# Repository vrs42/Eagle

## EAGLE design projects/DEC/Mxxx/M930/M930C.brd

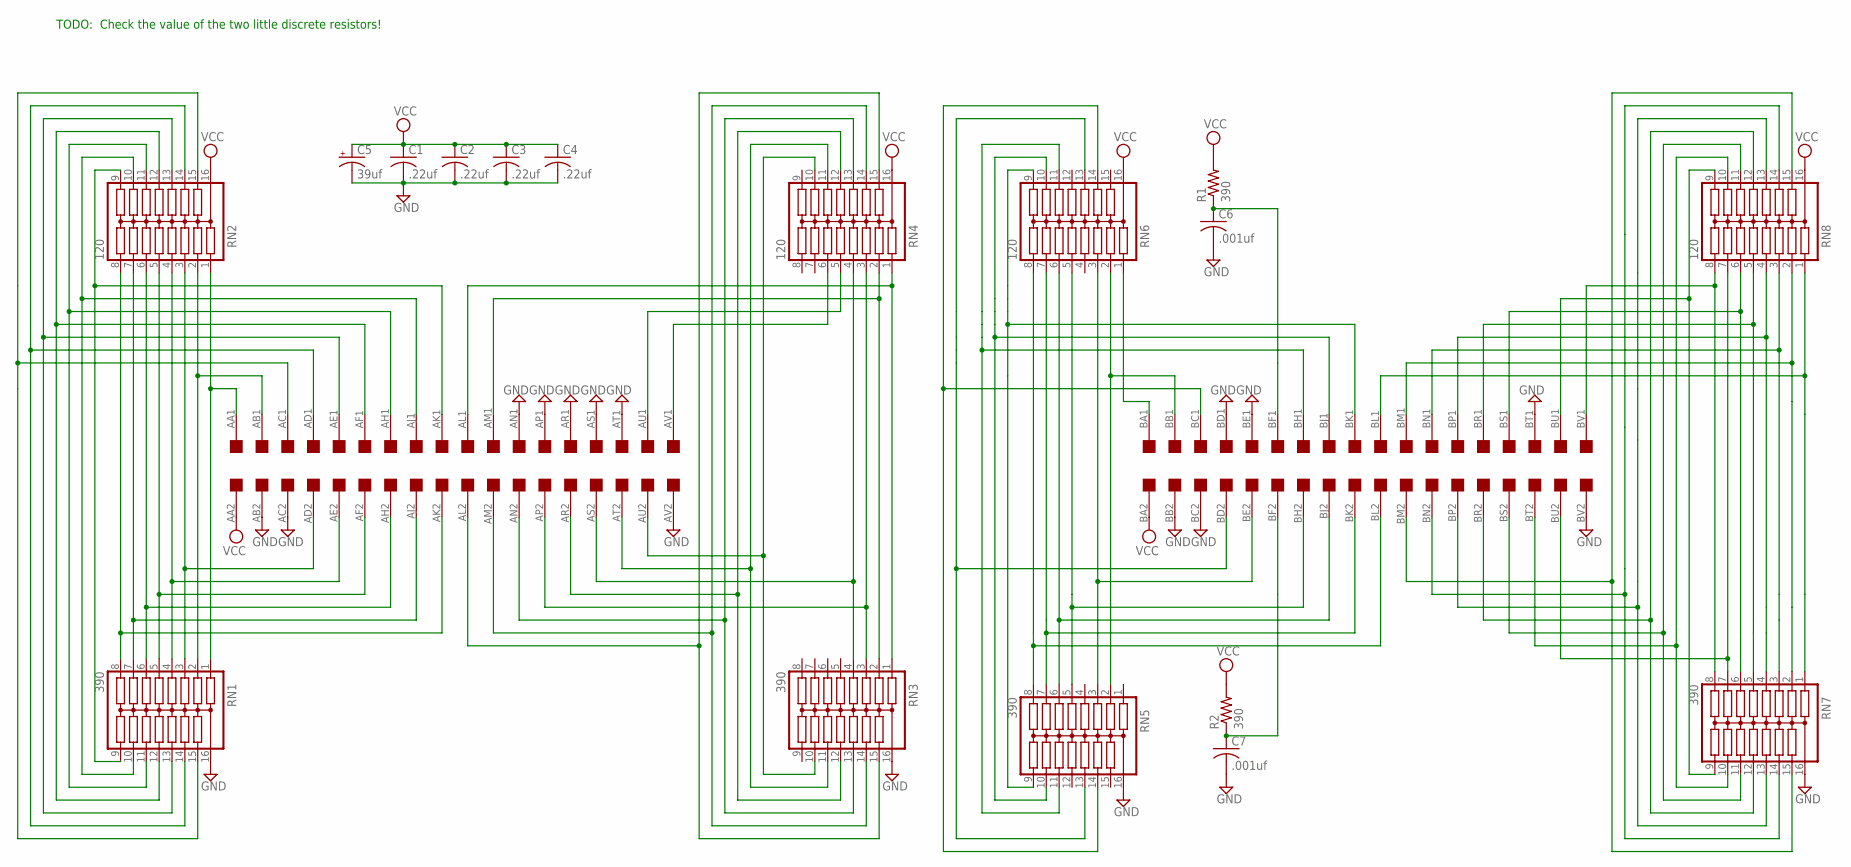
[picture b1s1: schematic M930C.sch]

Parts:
C1, C2, C3, C4: .22uf; C050-025X075
C5: 39uf; E15-5
C6, C7: .001uf; C050-025X075
R1, R2: 390; 0207/10
RN1, RN3, RN5, RN7: 390; DIL16
RN2, RN4, RN6, RN8: 120; DIL16
U$1: DOUBLE; EDGE-CON4

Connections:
AA1: RN1.1, RN2.1, U$1.AA1
AB1: RN1.2, RN2.2, U$1.AB1
AC1: RN1.15, RN2.15, U$1.AC1
AD1: RN1.14, RN2.14, U$1.AD1
AD2: RN1.3, RN2.3, U$1.AD2
AE1: RN1.13, RN2.13, U$1.AE1
AE2: RN1.4, RN2.4, U$1.AE2
AF1: RN1.12, RN2.12, U$1.AF1
AF2: RN1.5, RN2.5, U$1.AF2
AH1: RN1.11, RN2.11, U$1.AH1
AH2: RN1.6, RN2.6, U$1.AH2
AJ1: RN1.10, RN2.10, U$1.AJ1
AJ2: RN1.7, RN2.7, U$1.AJ2
AK1: RN1.9, RN2.9, U$1.AK1
AK2: RN1.8, RN2.8, U$1.AK2
AL1: RN3.1, RN4.1, U$1.AL1
AL2: RN3.15, RN4.15, U$1.AL2
AM1: RN3.2, RN4.2, U$1.AM1
AM2: RN3.14, RN4.14, U$1.AM2
AN2: RN3.13, RN4.13, U$1.AN2
AP2: RN3.3, RN4.3, U$1.AP2
AR2: RN3.12, RN4.12, U$1.AR2
AS2: RN3.4, RN4.4, U$1.AS2
AT2: RN3.11, RN4.11, U$1.AT2
AU1: RN4.5, U$1.AU1
AU2: RN3.10, RN4.10, U$1.AU2
AV1: RN4.6, U$1.AV1
BA1: RN6.1, U$1.BA1
BB1: RN5.2, RN6.2, U$1.BB1
BC1: RN5.14, RN6.14, U$1.BC1
BD2: RN5.13, RN6.13, U$1.BD2
BE2: RN5.3, RN6.3, U$1.BE2
BH1: RN5.11, RN6.11, U$1.BH1
BH2: RN5.5, RN6.5, U$1.BH2
BJ1: RN5.10, RN6.10, U$1.BJ1
BJ2: RN5.6, RN6.6, U$1.BJ2
BK1: RN5.9, RN6.9, U$1.BK1
BK2: RN5.7, RN6.7, U$1.BK2
BL1: RN7.1, RN8.1, U$1.BL1
BL2: RN5.8, RN6.8, U$1.BL2
BM1: RN7.2, RN8.2, U$1.BM1
BM2: RN7.15, RN8.15, U$1.BM2
BN1: RN7.3, RN8.3, U$1.BN1
BN2: RN7.14, RN8.14, U$1.BN2
BP1: RN7.4, RN8.4, U$1.BP1
BP2: RN7.13, RN8.13, U$1.BP2
BR1: RN7.5, RN8.5, U$1.BR1
BR2: RN7.12, RN8.12, U$1.BR2
BS1: RN7.6, RN8.6, U$1.BS1
BS2: RN7.11, RN8.11, U$1.BS2
BT2: RN7.10, RN8.10, U$1.BT2
BU1: RN7.9, RN8.9, U$1.BU1
BU2: RN7.7, RN8.7, U$1.BU2
BV1: RN7.8, RN8.8, U$1.BV1
GND: C1.2, C2.2, C3.2, C4.2, C5.-, C6.2, C7.2, RN1.16, RN3.16, RN5.16, RN7.16, U$1.AB2, U$1.AC2, U$1.AN1, U$1.AP1, U$1.AR1, U$1.AS1, U$1.AT1, U$1.AV2, U$1.BB2, U$1.BC2, U$1.BD1, U$1.BE1, U$1.BT1, U$1.BV2
unnamed: C7.1, R2.1, U$1.BF2
unnamed: C6.1, R1.1, U$1.BF1
VCC: C1.1, C2.1, C3.1, C4.1, C5.+, R1.2, R2.2, RN2.16, RN4.16, RN6.16, RN8.16, U$1.AA2, U$1.BA2

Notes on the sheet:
TODO: Check the value of the two little discrete resistors!

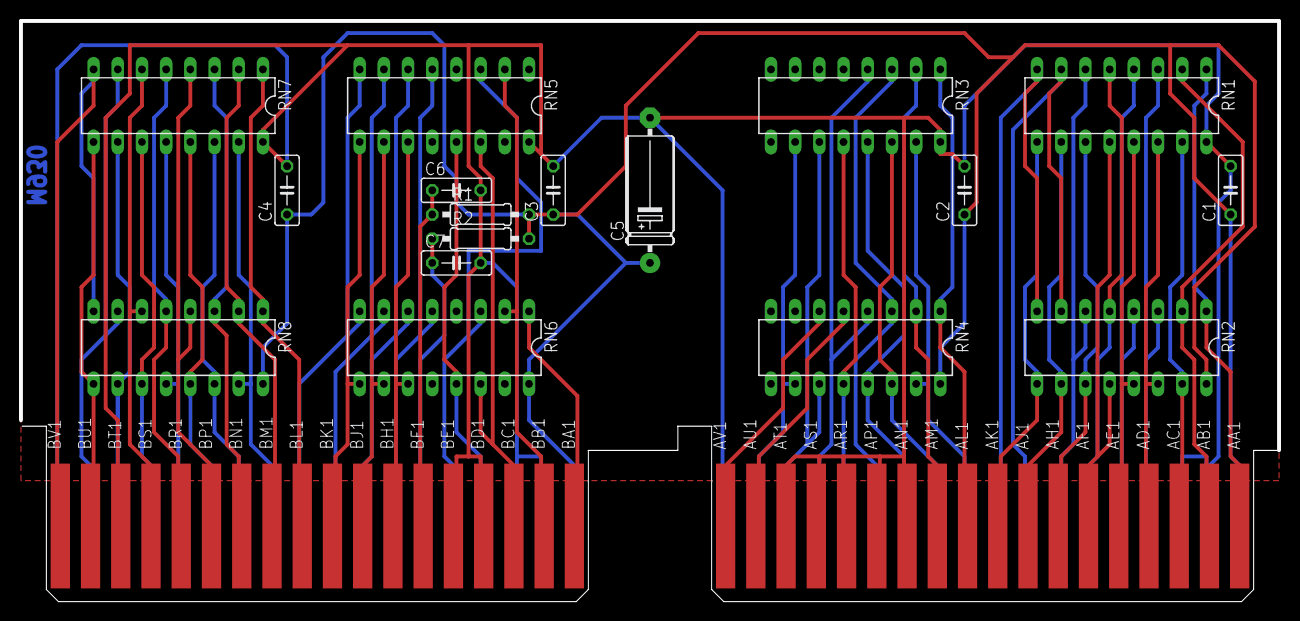
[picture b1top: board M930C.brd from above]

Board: 2 copper layers, 132.1 x 61.0 mm, 18 parts (0 on the bottom side), 58 nets.

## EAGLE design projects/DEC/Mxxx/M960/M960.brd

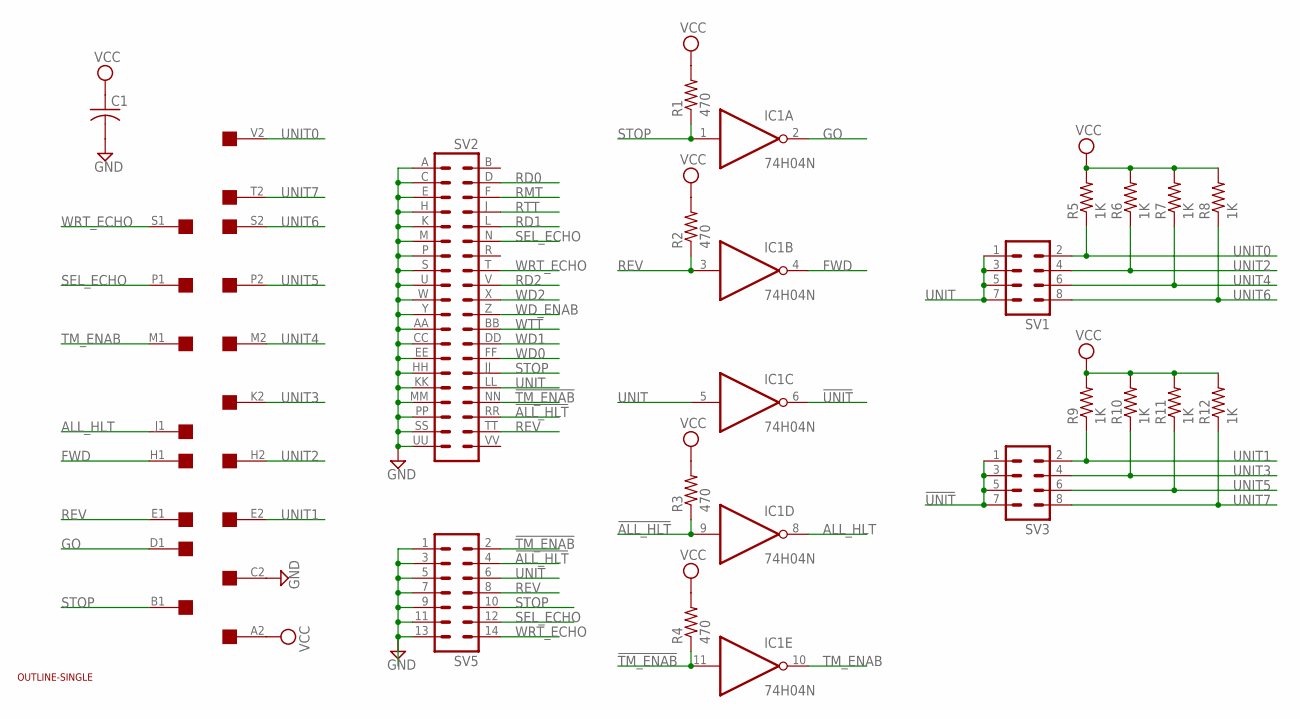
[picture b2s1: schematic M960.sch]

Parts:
C1: C-US050-025X075; C050-025X075
IC1: 74H04N; DIL14
R1, R2, R3, R4: 470; 0207/10
R5, R6, R7, R8, R9, R10, R11, R12: 1K; 0207/10
SV1, SV3: MA04-2
SV2: DEC40PINV
SV5: MA07-2
U$1: OUTLINE-SINGLE; SINGLE
U$2: SINGLE; EDGE-CON2

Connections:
!ALL_HLT: IC1.9 (I), R3.1, SV2.RR (36), SV5.4
!TM_ENAB: IC1.11 (I), R4.1, SV2.NN (34), SV5.2
!UNIT: IC1.6 (O), SV3.1, SV3.3, SV3.5, SV3.7
ALL_HLT: IC1.8 (O), U$2.J1
FWD: IC1.4 (O), U$2.H1
GND: C1.2, IC1.7 (GND), SV2.A (1), SV2.AA (23), SV2.C (3), SV2.CC (25), SV2.E (5), SV2.EE (27), SV2.H (7), SV2.HH (29), SV2.K (9), SV2.KK (31), SV2.M (11), SV2.MM (33), SV2.P (13), SV2.PP (35), SV2.S (15), SV2.SS (37), SV2.U (17), SV2.UU (39), SV2.W (19), SV2.Y (21), SV5.1, SV5.3, SV5.5, SV5.7, SV5.9, SV5.11, SV5.13, U$2.C2
GO: IC1.2 (O), U$2.D1
RD0: SV2.D (4)
RD1: SV2.L (10)
RD2: SV2.V (18)
REV: IC1.3 (I), R2.1, SV2.TT (38), SV5.8, U$2.E1
RMT: SV2.F (6)
RTT: SV2.J (8)
SEL_ECHO: SV2.N (12), SV5.12, U$2.P1
STOP: IC1.1 (I), R1.1, SV2.JJ (30), SV5.10, U$2.B1
TM_ENAB: IC1.10 (O), U$2.M1
UNIT: IC1.5 (I), SV1.1, SV1.3, SV1.5, SV1.7, SV2.LL (32), SV5.6
UNIT0: R5.1, SV1.2, U$2.V2
UNIT1: R9.1, SV3.2, U$2.E2
UNIT2: R6.1, SV1.4, U$2.H2
UNIT3: R10.1, SV3.4, U$2.K2
UNIT4: R7.1, SV1.6, U$2.M2
UNIT5: R11.1, SV3.6, U$2.P2
UNIT6: R8.1, SV1.8, U$2.S2
UNIT7: R12.1, SV3.8, U$2.T2
VCC: C1.1, IC1.14 (VCC), R1.2, R2.2, R3.2, R4.2, R5.2, R6.2, R7.2, R8.2, R9.2, R10.2, R11.2, R12.2, U$2.A2
WD0: SV2.FF (28)
WD1: SV2.DD (26)
WD2: SV2.X (20)
WD_ENAB: SV2.Z (22)
WRT_ECHO: SV2.T (16), SV5.14, U$2.S1
WTT: SV2.BB (24)

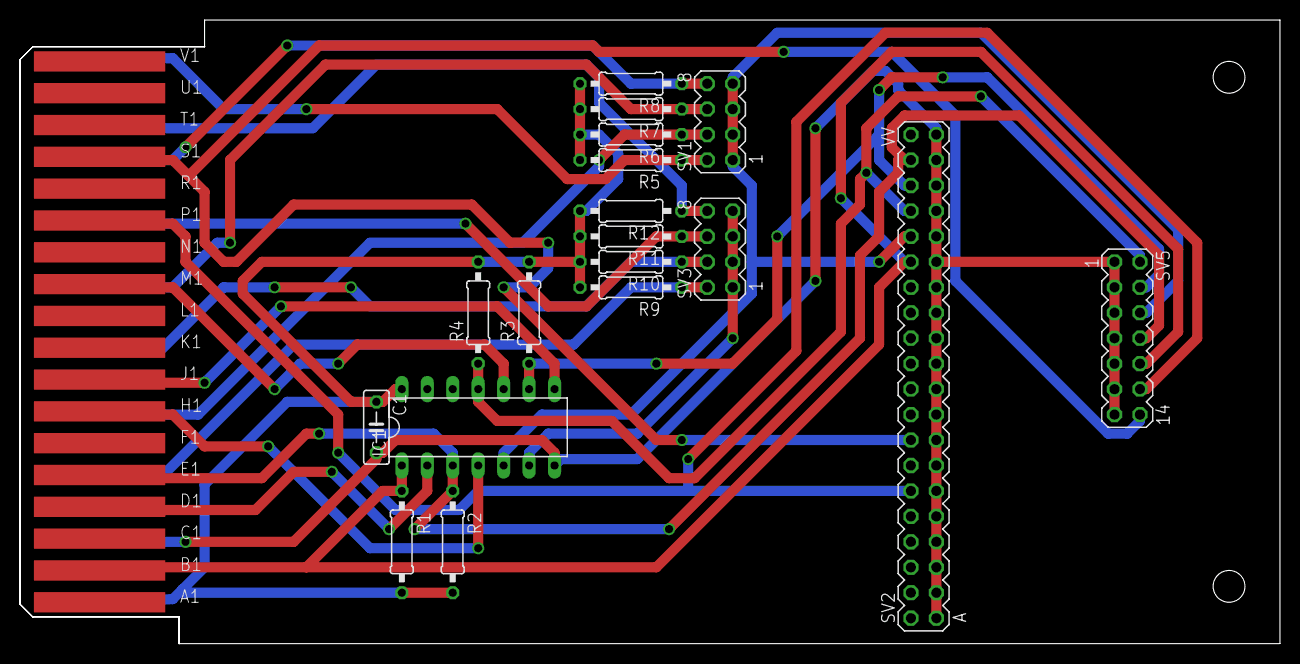
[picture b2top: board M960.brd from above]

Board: 2 copper layers, 125.7 x 62.2 mm, 20 parts (0 on the bottom side), 22 nets.

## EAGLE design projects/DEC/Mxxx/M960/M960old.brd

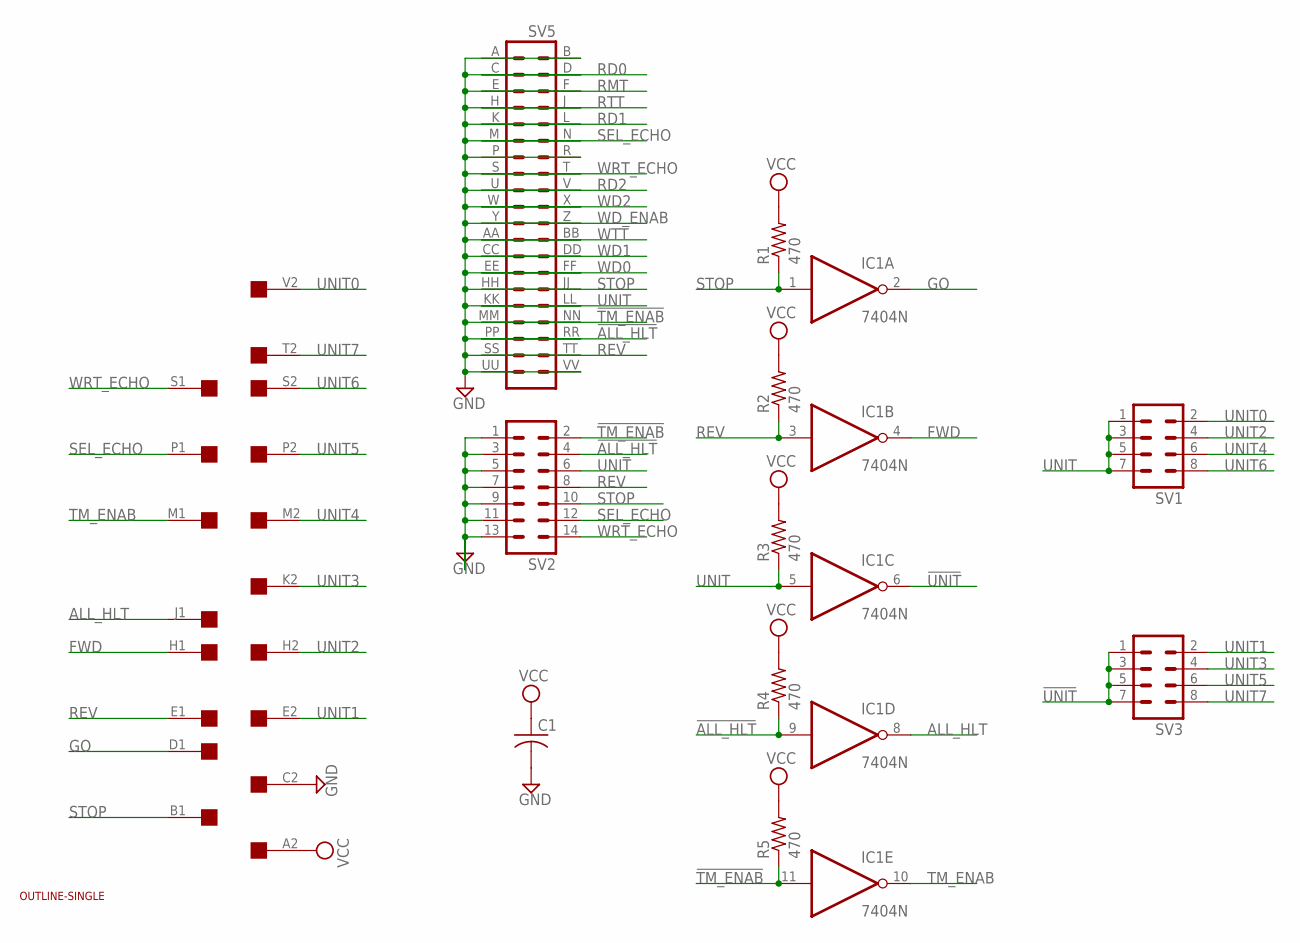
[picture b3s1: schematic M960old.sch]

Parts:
C1: C-US050-025X075; C050-025X075
IC1: 7404N; DIL14
R1, R2, R3, R4, R5: 470; 0207/10
SV1, SV3: MA04-2
SV2: MA07-2
SV5: DEC40PINV
U$1: OUTLINE-SINGLE; SINGLE
U$2: SINGLE; EDGE-CON2

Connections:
!ALL_HLT: IC1.9 (I), R4.1, SV2.4, SV5.PP (35)
!TM_ENAB: IC1.11 (I), R5.1, SV2.2, SV5.MM (33)
!UNIT: IC1.6 (O), SV3.1, SV3.3, SV3.5, SV3.7
ALL_HLT: IC1.8 (O), U$2.J1
FWD: IC1.4 (O), U$2.H1
GND: C1.2, IC1.7 (GND), SV2.1, SV2.3, SV2.5, SV2.7, SV2.9, SV2.11, SV2.13, SV5.B (2), SV5.BB (24), SV5.D (4), SV5.DD (26), SV5.F (6), SV5.FF (28), SV5.J (8), SV5.JJ (30), SV5.L (10), SV5.LL (32), SV5.N (12), SV5.NN (34), SV5.R (14), SV5.RR (36), SV5.T (16), SV5.TT (38), SV5.V (18), SV5.VV (40), SV5.X (20), SV5.Z (22), U$2.C2
GO: IC1.2 (O), U$2.D1
RD0: SV5.C (3)
RD1: SV5.K (9)
RD2: SV5.U (17)
REV: IC1.3 (I), R2.1, SV2.8, SV5.SS (37), U$2.E1
RMT: SV5.E (5)
RTT: SV5.H (7)
SEL_ECHO: SV2.12, SV5.M (11), U$2.P1
STOP: IC1.1 (I), R1.1, SV2.10, SV5.HH (29), U$2.B1
TM_ENAB: IC1.10 (O), U$2.M1
UNIT: IC1.5 (I), R3.1, SV1.1, SV1.3, SV1.5, SV1.7, SV2.6, SV5.KK (31)
UNIT0: SV1.2, U$2.V2
UNIT1: SV3.2, U$2.E2
UNIT2: SV1.4, U$2.H2
UNIT3: SV3.4, U$2.K2
UNIT4: SV1.6, U$2.M2
UNIT5: SV3.6, U$2.P2
UNIT6: SV1.8, U$2.S2
UNIT7: SV3.8, U$2.T2
VCC: C1.1, IC1.14 (VCC), R1.2, R2.2, R3.2, R4.2, R5.2, U$2.A2
WD0: SV5.EE (27)
WD1: SV5.CC (25)
WD2: SV5.W (19)
WD_ENAB: SV5.Y (21)
WRT_ECHO: SV2.14, SV5.S (15), U$2.S1
WTT: SV5.AA (23)

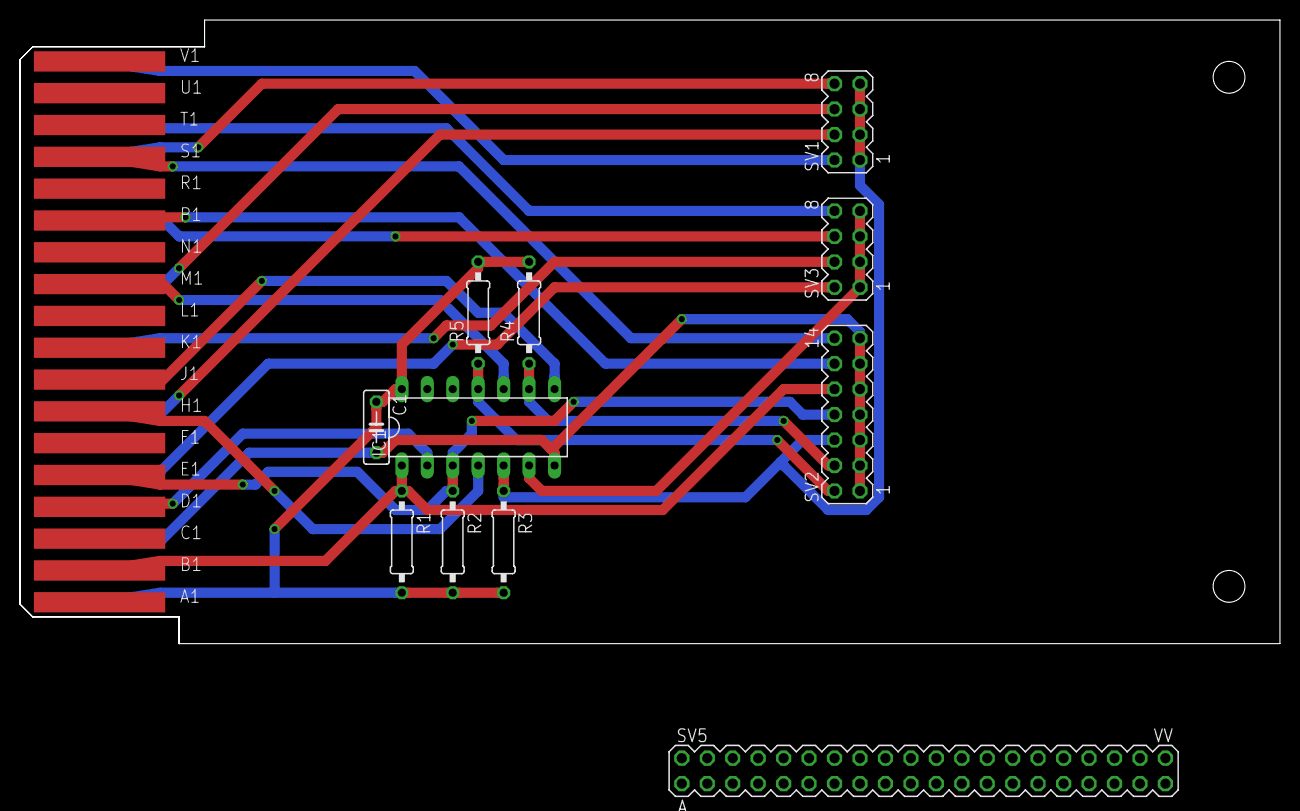
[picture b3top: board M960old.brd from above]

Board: 2 copper layers, 125.7 x 62.2 mm, 13 parts (0 on the bottom side), 22 nets.

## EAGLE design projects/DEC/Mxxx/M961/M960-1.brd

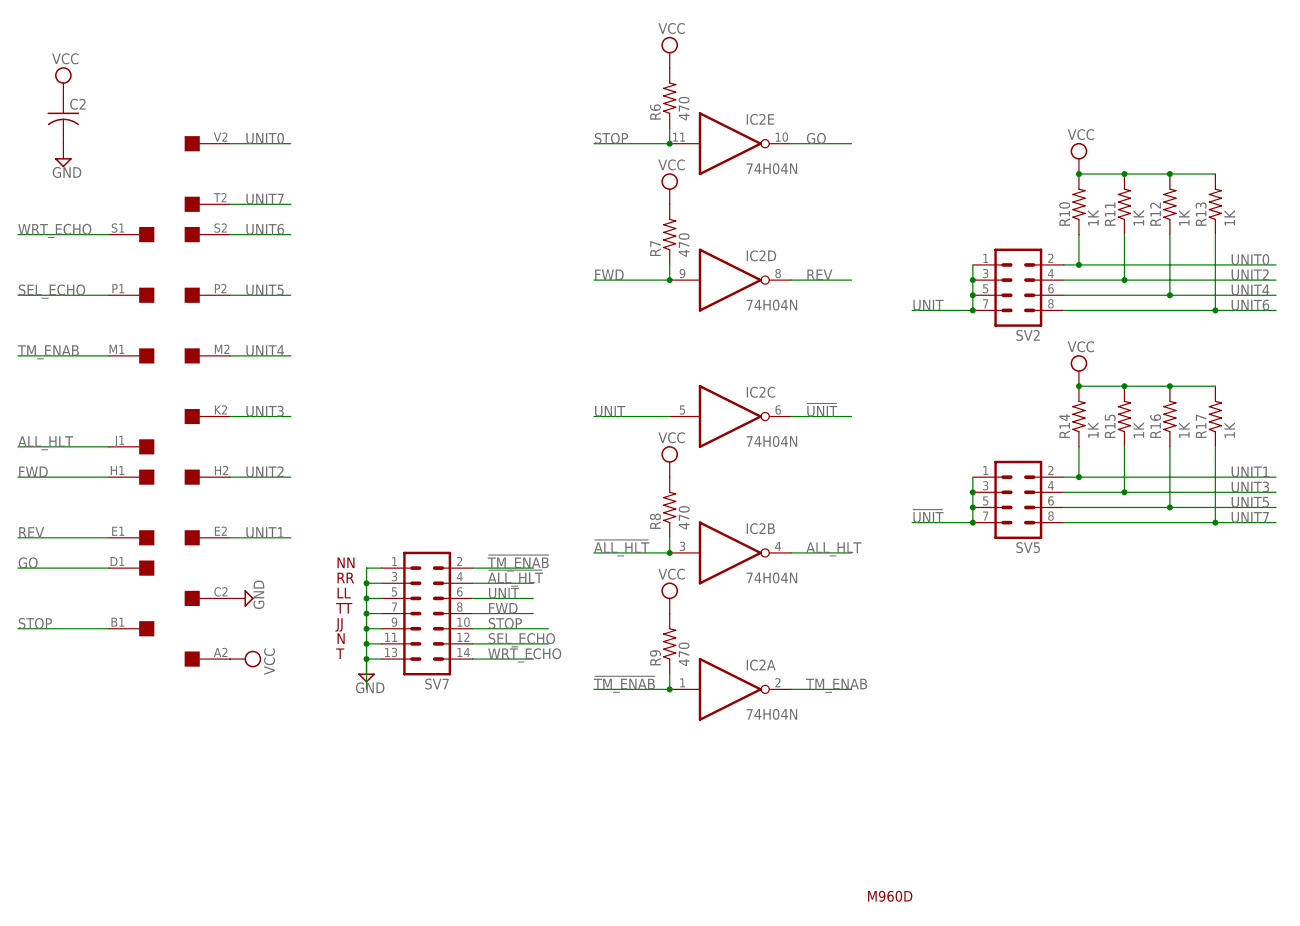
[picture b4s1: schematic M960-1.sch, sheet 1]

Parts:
C2: C-US050-025X075; C050-025X075
IC2: 74H04N; DIL14
R6, R7, R8, R9: 470; 0207/10
R10, R11, R12, R13, R14, R15, R16, R17: 1K; 0207/10
SV2, SV5: MA04-2
SV7: MA07-2
U$3: SINGLE; EDGE-CON2

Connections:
!ALL_HLT: IC2.3 (I), R8.1, SV7.4; also elsewhere on the board
!TM_ENAB: IC2.1 (I), R9.1, SV7.2; also elsewhere on the board
!UNIT: IC2.6 (O), SV5.1, SV5.3, SV5.5, SV5.7
ALL_HLT: IC2.4 (O), U$3.J1
FWD: IC2.9 (I), R7.1, SV7.8, U$3.H1; also elsewhere on the board
GND: C2.2, IC2.7 (GND), SV7.1, SV7.3, SV7.5, SV7.7, SV7.9, SV7.11, SV7.13, U$3.C2; also elsewhere on the board
GO: IC2.10 (O), U$3.D1
REV: IC2.8 (O), U$3.E1
SEL_ECHO: SV7.12, U$3.P1; also elsewhere on the board
STOP: IC2.11 (I), R6.1, SV7.10, U$3.B1; also elsewhere on the board
TM_ENAB: IC2.2 (O), U$3.M1
UNIT: IC2.5 (I), SV2.1, SV2.3, SV2.5, SV2.7, SV7.6; also elsewhere on the board
UNIT0: R10.1, SV2.2, U$3.V2
UNIT1: R14.1, SV5.2, U$3.E2
UNIT2: R11.1, SV2.4, U$3.H2
UNIT3: R15.1, SV5.4, U$3.K2
UNIT4: R12.1, SV2.6, U$3.M2
UNIT5: R16.1, SV5.6, U$3.P2
UNIT6: R13.1, SV2.8, U$3.S2
UNIT7: R17.1, SV5.8, U$3.T2
VCC: C2.1, IC2.14 (VCC), R6.2, R7.2, R8.2, R9.2, R10.2, R11.2, R12.2, R13.2, R14.2, R15.2, R16.2, R17.2, U$3.A2; also elsewhere on the board
WRT_ECHO: SV7.14, U$3.S1; also elsewhere on the board

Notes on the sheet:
M960D

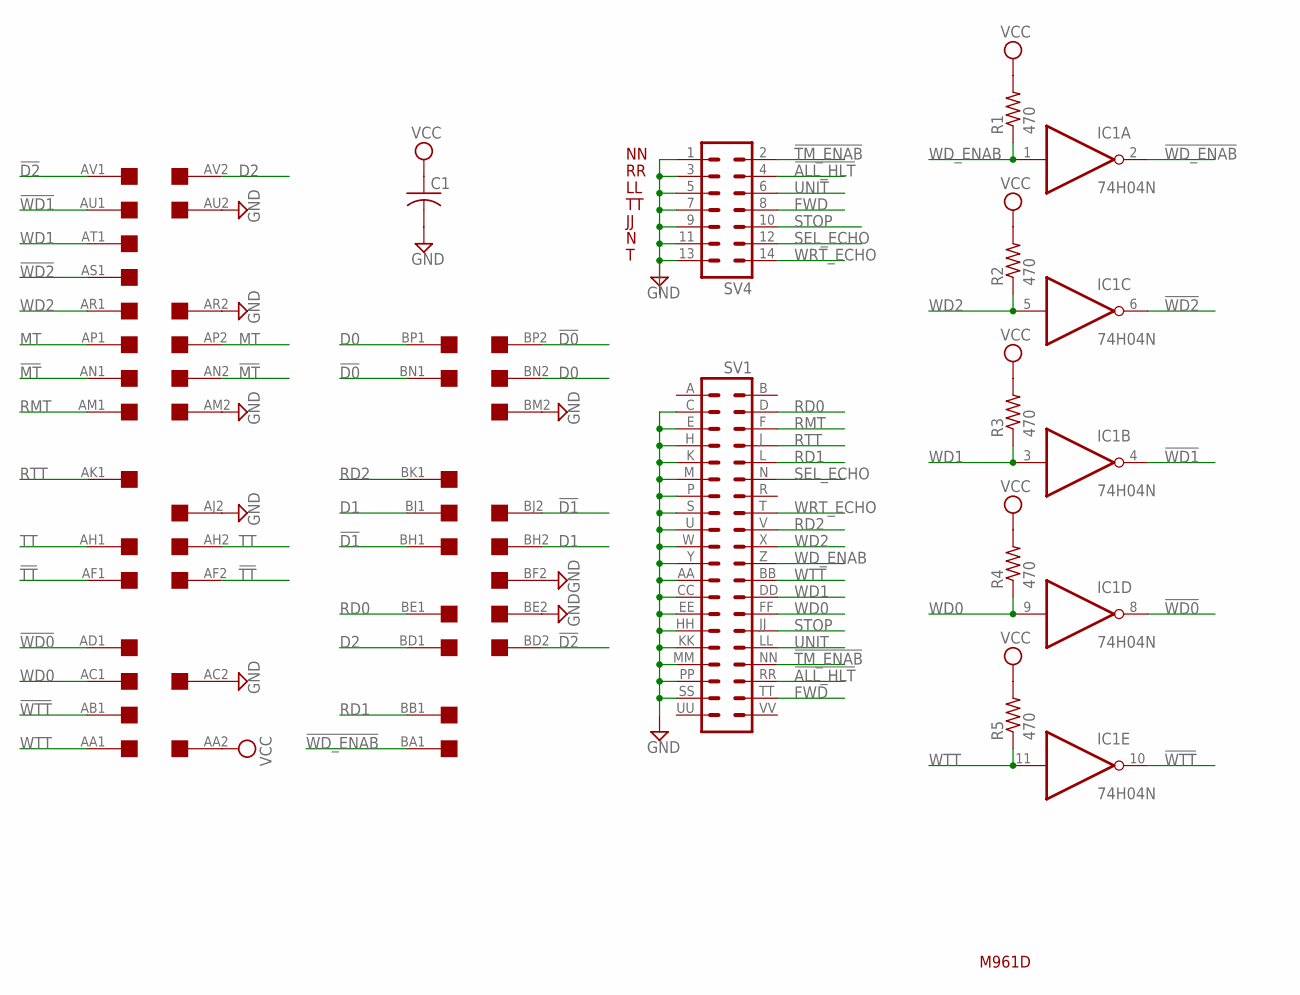
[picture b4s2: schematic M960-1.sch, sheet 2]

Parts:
C1: C-US050-025X075; C050-025X075
EDGE$1: DOUBLE; EDGE-CON4
IC1: 74H04N; DIL14
R1, R2, R3, R4, R5: 470; 0207/10
SV1: DEC40PINV
SV4: MA07-2

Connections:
!ALL_HLT: SV1.RR (36), SV4.4; also elsewhere on the board
!D0: EDGE$1.BN1, EDGE$1.BP2
!D1: EDGE$1.BH1, EDGE$1.BJ2
!D2: EDGE$1.AV1, EDGE$1.BD2
!MT: EDGE$1.AN1, EDGE$1.AN2
!TM_ENAB: SV1.NN (34), SV4.2; also elsewhere on the board
!TT: EDGE$1.AF1, EDGE$1.AF2
!WD0: EDGE$1.AD1, IC1.8 (O)
!WD1: EDGE$1.AU1, IC1.4 (O)
!WD2: EDGE$1.AS1, IC1.6 (O)
!WD_ENAB: EDGE$1.BA1, IC1.2 (O)
!WTT: EDGE$1.AB1, IC1.10 (O)
D0: EDGE$1.BN2, EDGE$1.BP1
D1: EDGE$1.BH2, EDGE$1.BJ1
D2: EDGE$1.AV2, EDGE$1.BD1
FWD: SV1.TT (38), SV4.8; also elsewhere on the board
GND: C1.2, EDGE$1.AC2, EDGE$1.AJ2, EDGE$1.AM2, EDGE$1.AR2, EDGE$1.AU2, EDGE$1.BE2, EDGE$1.BF2, EDGE$1.BM2, IC1.7 (GND), SV1.AA (23), SV1.C (3), SV1.CC (25), SV1.E (5), SV1.EE (27), SV1.H (7), SV1.HH (29), SV1.K (9), SV1.KK (31), SV1.M (11), SV1.MM (33), SV1.P (13), SV1.PP (35), SV1.S (15), SV1.SS (37), SV1.U (17), SV1.W (19), SV1.Y (21), SV4.1, SV4.3, SV4.5, SV4.7, SV4.9, SV4.11, SV4.13; also elsewhere on the board
MT: EDGE$1.AP1, EDGE$1.AP2
RD0: EDGE$1.BE1, SV1.D (4)
RD1: EDGE$1.BB1, SV1.L (10)
RD2: EDGE$1.BK1, SV1.V (18)
RMT: EDGE$1.AM1, SV1.F (6)
RTT: EDGE$1.AK1, SV1.J (8)
SEL_ECHO: SV1.N (12), SV4.12; also elsewhere on the board
STOP: SV1.JJ (30), SV4.10; also elsewhere on the board
TT: EDGE$1.AH1, EDGE$1.AH2
UNIT: SV1.LL (32), SV4.6; also elsewhere on the board
VCC: C1.1, EDGE$1.AA2, IC1.14 (VCC), R1.2, R2.2, R3.2, R4.2, R5.2; also elsewhere on the board
WD0: EDGE$1.AC1, IC1.9 (I), R4.1, SV1.FF (28)
WD1: EDGE$1.AT1, IC1.3 (I), R3.1, SV1.DD (26)
WD2: EDGE$1.AR1, IC1.5 (I), R2.1, SV1.X (20)
WD_ENAB: IC1.1 (I), R1.1, SV1.Z (22)
WRT_ECHO: SV1.T (16), SV4.14; also elsewhere on the board
WTT: EDGE$1.AA1, IC1.11 (I), R5.1, SV1.BB (24)

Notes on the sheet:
M961D

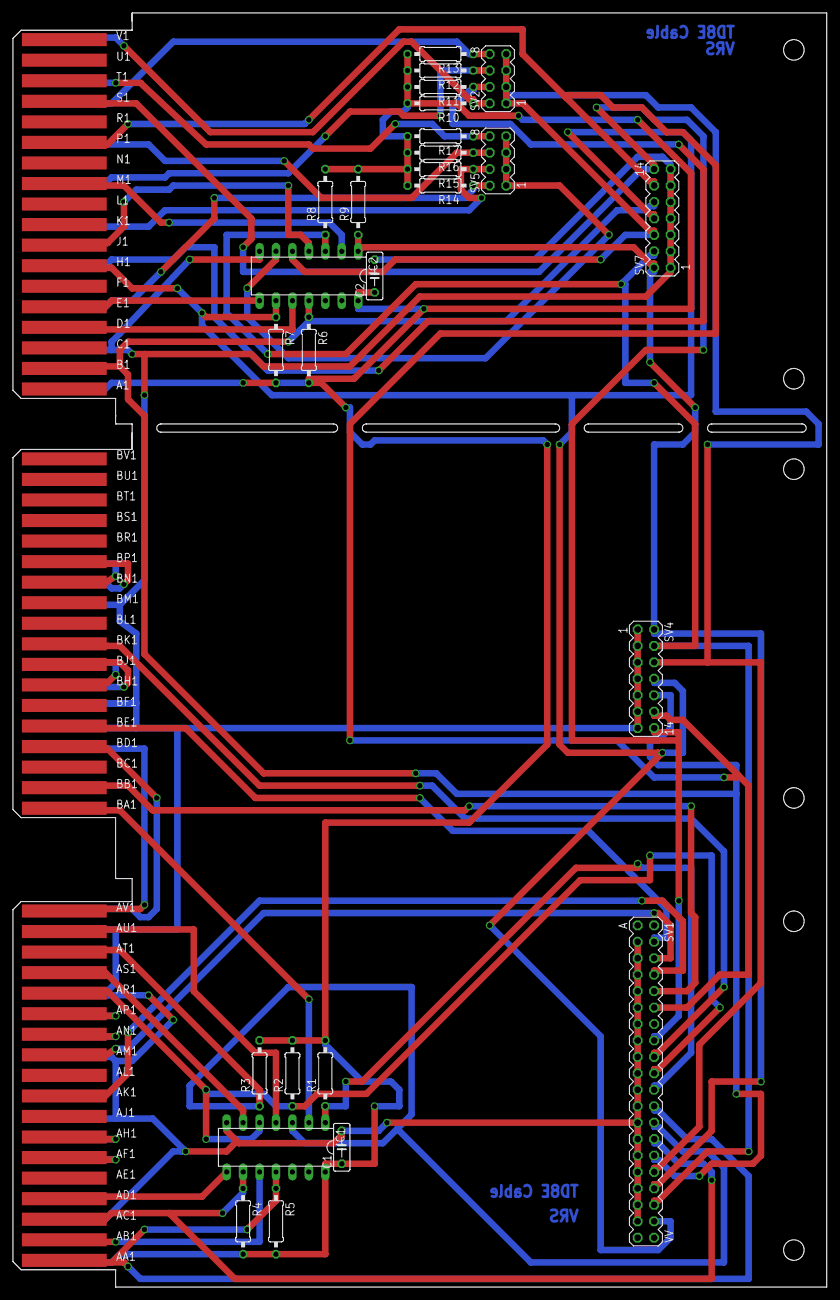
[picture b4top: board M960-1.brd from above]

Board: 2 copper layers, 125.7 x 196.8 mm, 28 parts (0 on the bottom side), 47 nets.

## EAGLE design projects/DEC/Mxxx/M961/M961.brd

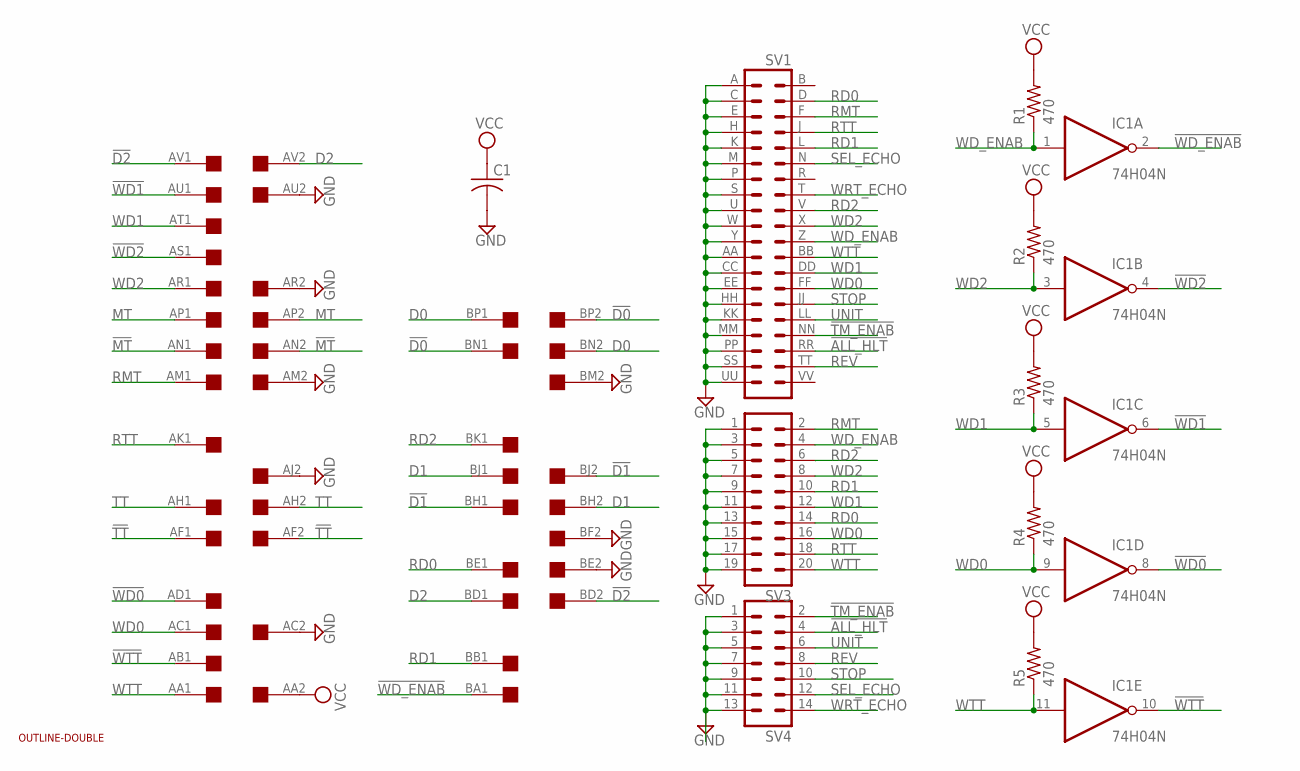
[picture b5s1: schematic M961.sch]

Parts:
C1: C-US050-025X075; C050-025X075
EDGE$1: DOUBLE; EDGE-CON4
IC1: 74H04N; DIL14
R1, R2, R3, R4, R5: 470; 0207/10
SV1: DEC40PINV
SV3: MA10-2
SV4: MA07-2
U$2: OUTLINE-DOUBLE; DOUBLE

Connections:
!ALL_HLT: SV1.RR (36), SV4.4
!D0: EDGE$1.BN1, EDGE$1.BP2
!D1: EDGE$1.BH1, EDGE$1.BJ2
!D2: EDGE$1.AV1, EDGE$1.BD2
!MT: EDGE$1.AN1, EDGE$1.AN2
!TM_ENAB: SV1.NN (34), SV4.2
!TT: EDGE$1.AF1, EDGE$1.AF2
!WD0: EDGE$1.AD1, IC1.8 (O)
!WD1: EDGE$1.AU1, IC1.6 (O)
!WD2: EDGE$1.AS1, IC1.4 (O)
!WD_ENAB: EDGE$1.BA1, IC1.2 (O)
!WTT: EDGE$1.AB1, IC1.10 (O)
D0: EDGE$1.BN2, EDGE$1.BP1
D1: EDGE$1.BH2, EDGE$1.BJ1
D2: EDGE$1.AV2, EDGE$1.BD1
GND: C1.2, EDGE$1.AC2, EDGE$1.AJ2, EDGE$1.AM2, EDGE$1.AR2, EDGE$1.AU2, EDGE$1.BE2, EDGE$1.BF2, EDGE$1.BM2, IC1.7 (GND), SV1.A (1), SV1.AA (23), SV1.C (3), SV1.CC (25), SV1.E (5), SV1.EE (27), SV1.H (7), SV1.HH (29), SV1.K (9), SV1.KK (31), SV1.M (11), SV1.MM (33), SV1.P (13), SV1.PP (35), SV1.S (15), SV1.SS (37), SV1.U (17), SV1.UU (39), SV1.W (19), SV1.Y (21), SV3.1, SV3.3, SV3.5, SV3.7, SV3.9, SV3.11, SV3.13, SV3.15, SV3.17, SV3.19, SV4.1, SV4.3, SV4.5, SV4.7, SV4.9, SV4.11, SV4.13
MT: EDGE$1.AP1, EDGE$1.AP2
RD0: EDGE$1.BE1, SV1.D (4), SV3.14
RD1: EDGE$1.BB1, SV1.L (10), SV3.10
RD2: EDGE$1.BK1, SV1.V (18), SV3.6
REV: SV1.TT (38), SV4.8
RMT: EDGE$1.AM1, SV1.F (6), SV3.2
RTT: EDGE$1.AK1, SV1.J (8), SV3.18
SEL_ECHO: SV1.N (12), SV4.12
STOP: SV1.JJ (30), SV4.10
TT: EDGE$1.AH1, EDGE$1.AH2
UNIT: SV1.LL (32), SV4.6
VCC: C1.1, EDGE$1.AA2, IC1.14 (VCC), R1.2, R2.2, R3.2, R4.2, R5.2
WD0: EDGE$1.AC1, IC1.9 (I), R4.1, SV1.FF (28), SV3.16
WD1: EDGE$1.AT1, IC1.5 (I), R3.1, SV1.DD (26), SV3.12
WD2: EDGE$1.AR1, IC1.3 (I), R2.1, SV1.X (20), SV3.8
WD_ENAB: IC1.1 (I), R1.1, SV1.Z (22), SV3.4
WRT_ECHO: SV1.T (16), SV4.14
WTT: EDGE$1.AA1, IC1.11 (I), R5.1, SV1.BB (24), SV3.20

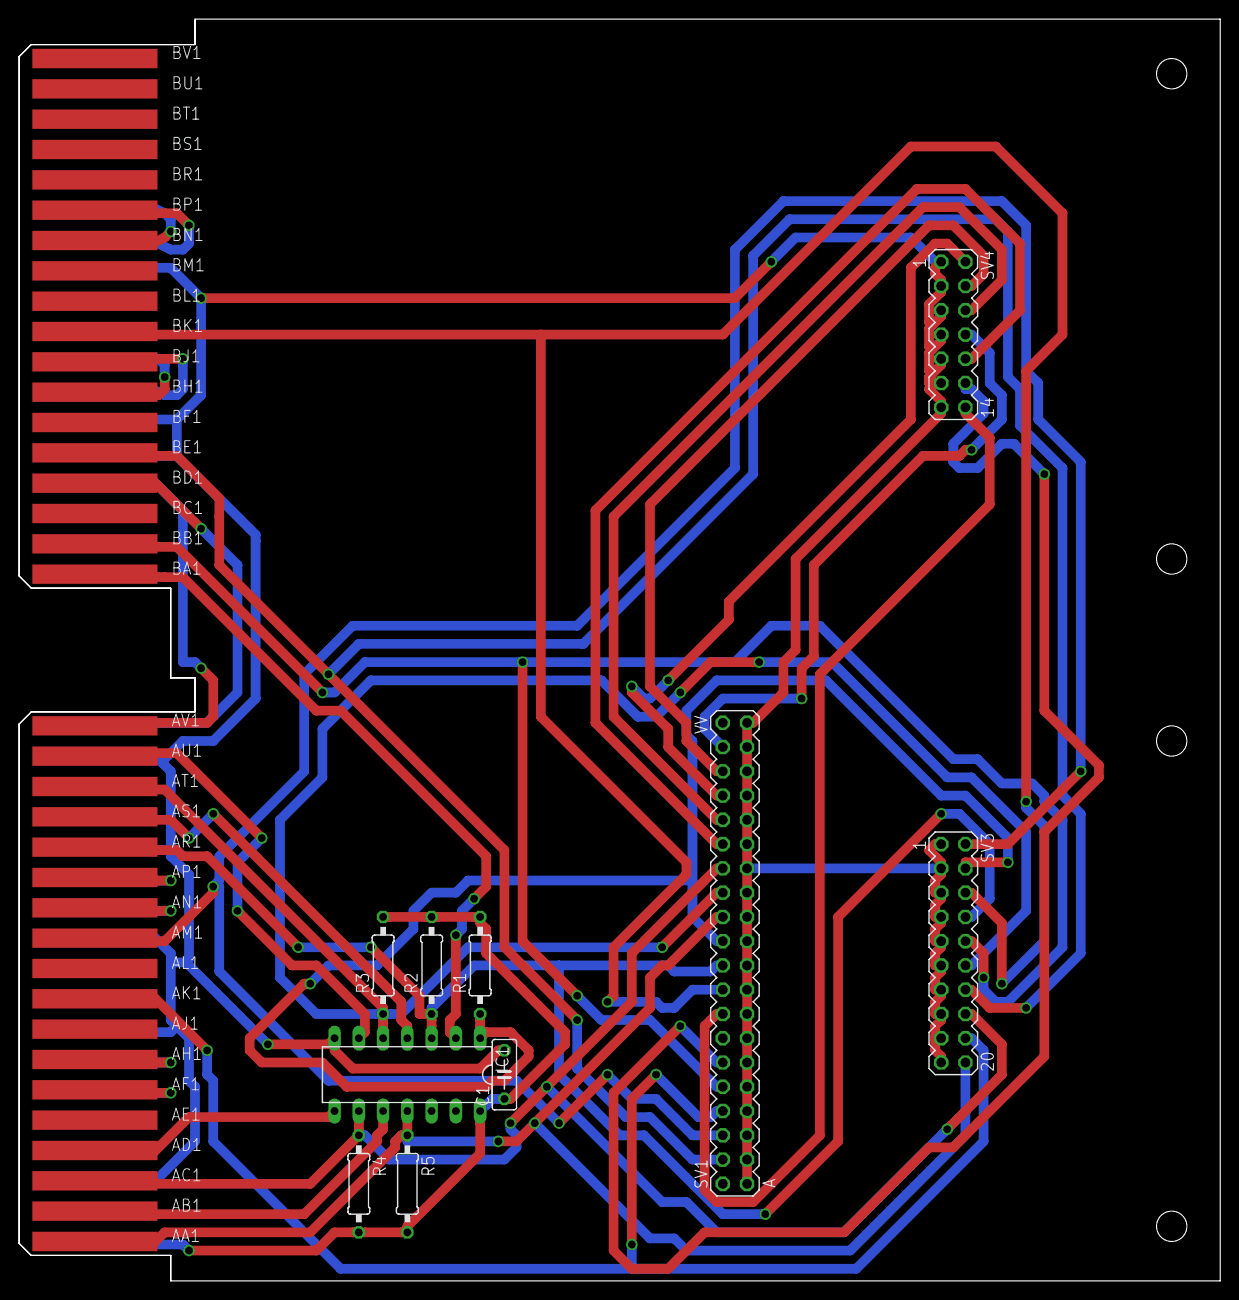
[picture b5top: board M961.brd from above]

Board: 2 copper layers, 125.7 x 132.1 mm, 12 parts (0 on the bottom side), 34 nets.

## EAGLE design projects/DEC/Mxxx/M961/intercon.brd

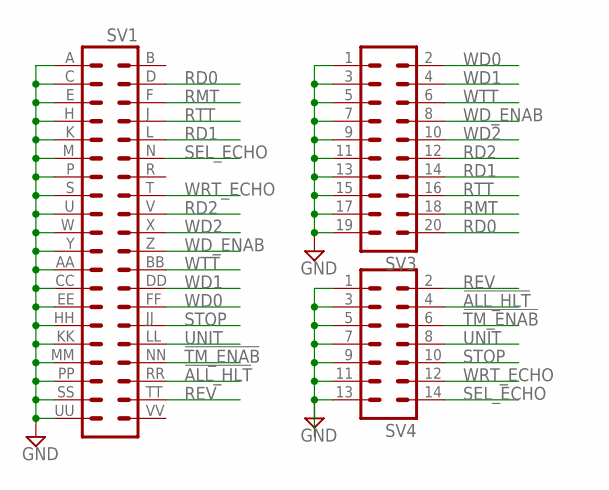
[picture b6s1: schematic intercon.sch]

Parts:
SV1: DEC40PINV
SV3: MA10-2
SV4: MA07-2

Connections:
!ALL_HLT: SV1.RR (36), SV4.4
!TM_ENAB: SV1.NN (34), SV4.6
GND: SV1.A (1), SV1.AA (23), SV1.C (3), SV1.CC (25), SV1.E (5), SV1.EE (27), SV1.H (7), SV1.HH (29), SV1.K (9), SV1.KK (31), SV1.M (11), SV1.MM (33), SV1.P (13), SV1.PP (35), SV1.S (15), SV1.SS (37), SV1.U (17), SV1.UU (39), SV1.W (19), SV1.Y (21), SV3.1, SV3.3, SV3.5, SV3.7, SV3.9, SV3.11, SV3.13, SV3.15, SV3.17, SV3.19, SV4.1, SV4.3, SV4.5, SV4.7, SV4.9, SV4.11, SV4.13
RD0: SV1.D (4), SV3.20
RD1: SV1.L (10), SV3.14
RD2: SV1.V (18), SV3.12
REV: SV1.TT (38), SV4.2
RMT: SV1.F (6), SV3.18
RTT: SV1.J (8), SV3.16
SEL_ECHO: SV1.N (12), SV4.14
STOP: SV1.JJ (30), SV4.10
UNIT: SV1.LL (32), SV4.8
WD0: SV1.FF (28), SV3.2
WD1: SV1.DD (26), SV3.4
WD2: SV1.X (20), SV3.10
WD_ENAB: SV1.Z (22), SV3.8
WRT_ECHO: SV1.T (16), SV4.12
WTT: SV1.BB (24), SV3.6

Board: 2 copper layers, 3 parts (0 on the bottom side), 18 nets, no tracks yet.
